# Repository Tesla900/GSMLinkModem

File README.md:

# GSMLinkModem
EFM32TG222F32-QFP48T+BC66-NA/M66 GSM/GPRS/NB-IoT board

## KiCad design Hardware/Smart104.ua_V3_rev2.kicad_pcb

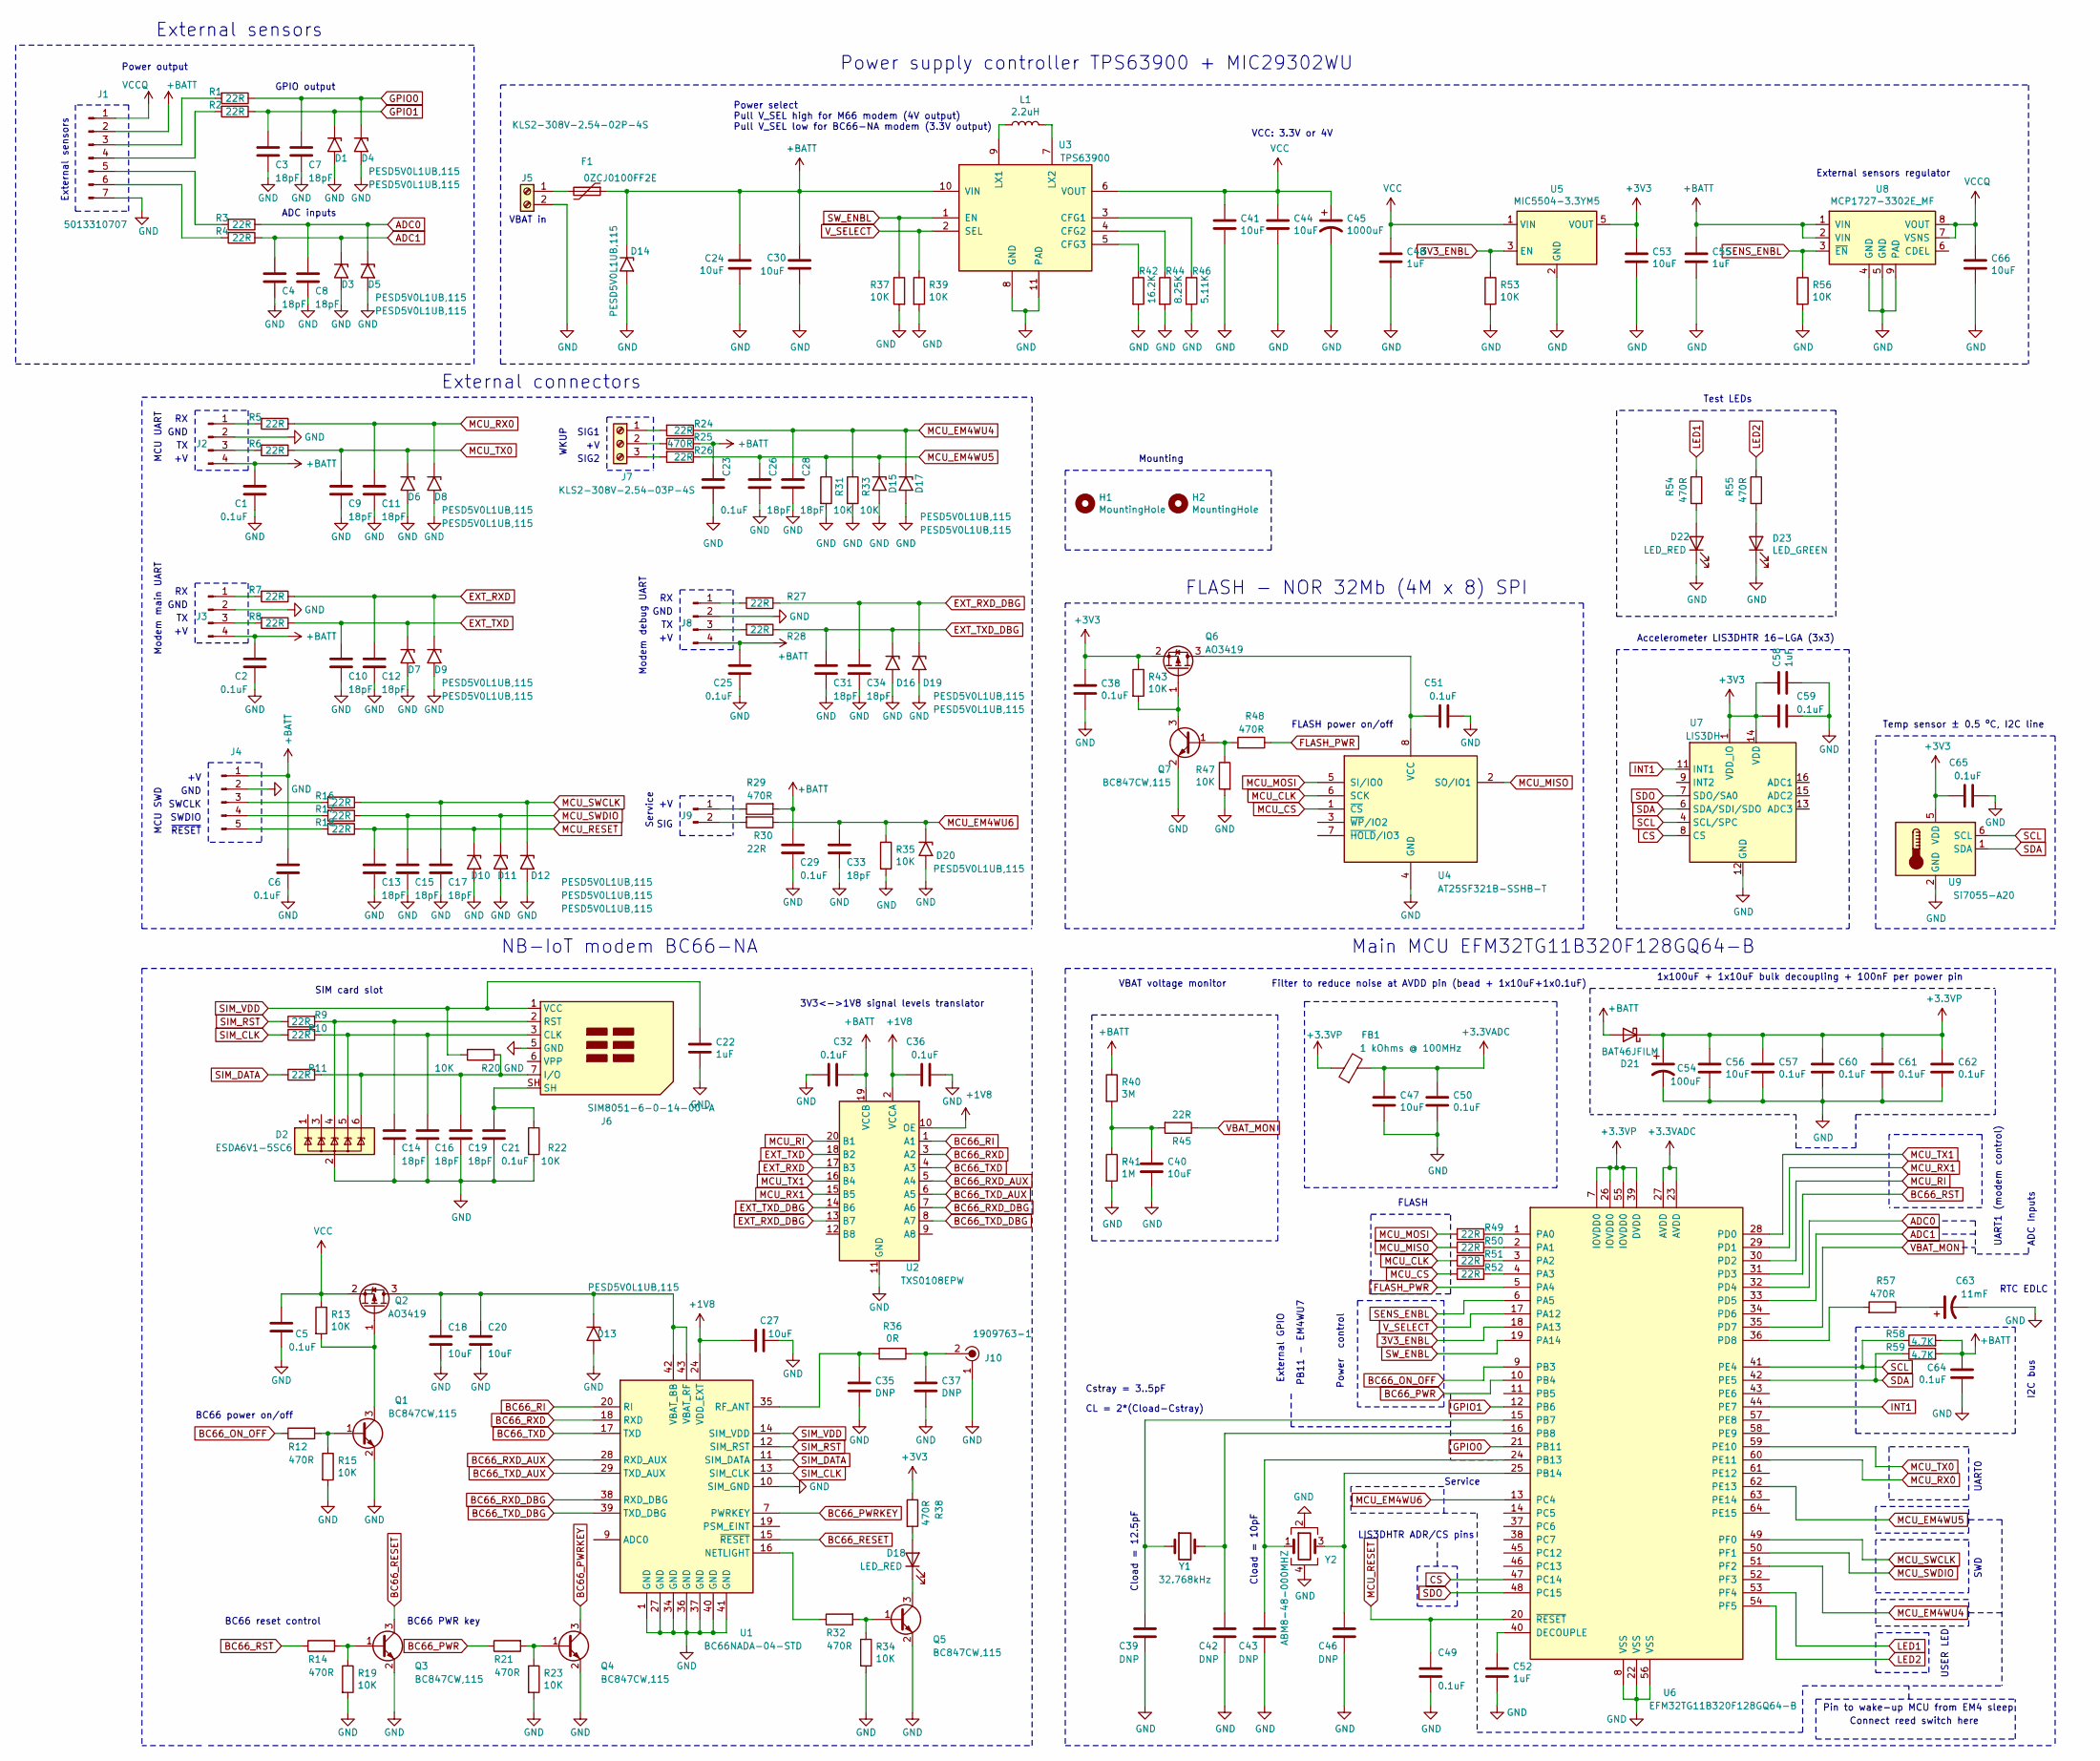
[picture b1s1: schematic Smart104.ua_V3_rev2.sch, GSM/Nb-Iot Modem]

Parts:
C1, C2, C5, C6, C21, C23, C25, C29, C32, C36, C38, C49, C50, C51, C57, C59, C60, C61, C62, C64, C65: 0.1uF; C_0402_1005Metric; Voltage 25V; PartNumber CC0402KRX7R7BB104
C3, C4, C7, C8, C9, C10, C11, C12, C13, C14, C15, C16, C17, C19, C26, C28, C31, C33, C34: 18pF; C_0402_1005Metric; Voltage 50V; PartNumber CC0402JRNPO9BN180
C18, C20, C24, C27, C30, C40, C41, C44, C47, C53, C56, C66: 10uF; C_0805_2012Metric; Voltage 25V; PartNumber CC0805MKX7R7BB106
C22, C48, C52, C55, C58: 1uF; C_0603_1608Metric; Voltage 25V; PartNumber CC0603KRX7R7BB105
C35, C37: DNP; C_0402_1005Metric
C39, C42, C43, C46: DNP; C_0402_1005Metric; Voltage 50V
C45: 1000uF; CP_Radial_D8.0mm_P3.50mm; Voltage 6.3V; PartNumber A750KK108M0JAAE015
C54: 100uF; CP_EIA-3216-18_Kemet-A; Voltage 6.3V; PartNumber TCJA107M006R0150E
C63: 11mF; CAPCP3225X100N; Voltage 3.3V; PartNumber CPH3225A
D1, D3, D4, D5, D6, D7, D8, D9, D10, D11, D12, D13, D14, D15, D16, D17, D19, D20: PESD5V0L1UB,115; D_SOD-523; PartNumber PESD5V0L1UB,115
D2: ESDA6V1-5SC6; SOT-23-6; PartNumber ESDA6V1-5SC6
D18, D22: LED_RED; LED_0603_1608Metric; PartNumber APT1608SURCK
D21: BAT46JFILM; D_SOD-323; PartNumber BAT46JFILM
D23: LED_GREEN; LED_0603_1608Metric; PartNumber APT1608CGCK
F1: 0ZCJ0100FF2E; Fuse_1206_3216Metric; PartNumber 0ZCJ0100FF2E
FB1: 1 kOhms @ 100MHz; L_0402_1005Metric; PartNumber BLM15AG102SN1D
H1, H2: MountingHole; MountingHole_3.2mm_M3; PartNumber Mounting screw M3 DIN965
J1: 5013310707; Molex_Pico-Clasp_501331-0707_1x07-1MP_P1.00mm_Vertical; PartNumber 5013310707
J2, J3, J8: KLS1-207-1-04-S; PinHeader_1x04_P2.54mm_Vertical; PartNumber KLS1-207-1-04-S
J4: KLS1-207-1-05-S; PinHeader_1x05_P2.54mm_Vertical; PartNumber KLS1-207-1-05-S
J5: KLS2-308V-2.54-02P-4S; TerminalBlock_TE_282834-2_1x02_P2.54mm_Horizontal; PartNumber KLS2-308V-2.54-02P-4S
J6: SIM8051-6-0-14-00-A; GCT_SIM8051-6-0-14-00-X-REVD; PartNumber SIM8051-6-0-14-00-A
J7: KLS2-308V-2.54-03P-4S; TerminalBlock_TE_282834-3_1x03_P2.54mm_Horizontal; PartNumber KLS2-308V-2.54-03P-4S
J9: KLS1-207-1-02-S; PinHeader_1x02_P2.54mm_Vertical; PartNumber KLS1-207-1-02-S
J10: 1909763-1; UMCoax_Pin_1909763-1; PartNumber 1909763-1
L1: 2.2uH; L_1008_2520Metric_Pad1.43x2.20mm_HandSolder; PartNumber DFE252010F-2R2M=P2
Q1, Q3, Q4, Q5, Q7: BC847CW,115; SOT-323_SC-70; PartNumber BC847CW,115
Q2, Q6: AO3419; SOT-23; PartNumber AO3419
R1, R2, R3, R4, R5, R6, R7, R8, R9, R10, R11, R16, R17, R18, R24, R26, R27, R28, R30, R45, R49, R50, R51, R52: 22R; R_0402_1005Metric; PartNumber RC0402JR-0722RL
R12, R14, R21, R25, R29, R32, R38, R48, R54, R55, R57: 470R; R_0402_1005Metric; PartNumber RC0402FR-07470RL
R13, R15, R19, R20, R22, R23, R31, R33, R34, R35, R37, R39, R43, R47, R53, R56: 10K; R_0402_1005Metric; PartNumber RC0402FR-0710KL
R36: 0R; R_0402_1005Metric; PartNumber RC0402JR-070RL
R40: 3M; R_0402_1005Metric; PartNumber RC0402FR-073ML
R41: 1M; R_0402_1005Metric; PartNumber RC0402FR-071ML
R42: 16.2K; R_0402_1005Metric; PartNumber RC0402FR-0716K2L
R44: 8.25K; R_0402_1005Metric; PartNumber RC0402FR-078K25L
R46: 5.11K; R_0402_1005Metric; PartNumber RC0402FR-075K11L
R58, R59: 4.7K; R_0402_1005Metric; PartNumber RC0402JR-074K7L
U1: BC66NADA-04-STD; Quectel_BC66; PartNumber BC66NADA-04-STD
U2: TXS0108EPW; TSSOP-20_4.4x6.5mm_P0.65mm; PartNumber TXS0108EPW
U3: TPS63900; DFN-10-1EP_3x3mm_P0.5mm_EP1.65x2.38mm_ThermalVias; PartNumber TPS63900DSKR
U4: AT25SF321B-SSHB-T; SOIC-8_3.9x4.9mm_P1.27mm; PartNumber AT25SF321B-SSHB-T
U5: MIC5504-3.3YM5; SOT-23-5; PartNumber MIC5504-3.3YM5
U6: EFM32TG11B320F128GQ64-B; TQFP-64_10x10mm_P0.5mm; PartNumber EFM32TG11B320F128GQ64-B
U7: LIS3DH; LGA-16_3x3mm_P0.5mm_fixed; PartNumber LIS3DH
U8: MCP1727-3302E_MF; VDFN-8-1EP_2x2mm_P0.5mm_EP0.9x1.7mm; PartNumber MCP1727-3302E_MF
U9: Si7055-A20; DFN-6-1EP_3x3mm_P1mm_EP1.5x2.4mm; PartNumber Si7055-A20
Y1: 32.768kHz; Crystal_SMD_3215-2Pin_3.2x1.5mm; PartNumber CM315D32768DZFT
Y2: ABM8-48-000MHZ; Crystal_SMD_3225-4Pin_3.2x2.5mm; PartNumber ABM8-48.000MHZ-10-1-U-T

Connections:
3V3_ENBL: R53.1, U5.3 (EN), U6.18 (PA13)
+1V8: C27.1, C36.1, U1.24 (VDD_EXT), U2.2 (VCCA), U2.10 (OE)
+3.3VADC: C47.1, C50.1, FB1.2, U6.23 (AVDD), U6.27 (AVDD)
+3.3VP: C54.1, C56.1, C57.1, C60.1, C61.1, C62.1, D21.1 (K), FB1.1, U6.7 (IOVDD0), U6.26 (IOVDD0), U6.39 (DVDD), U6.55 (IOVDD0)
+3V3: C38.1, C53.1, C58.1, C59.2, C65.1, Q6.2 (S), R38.1, R43.1, U5.5 (VOUT), U7.1 (VDD_IO), U7.14 (VDD), U9.5 (VDD)
+BATT: C1.1, C2.1, C6.1, C23.1, C24.1, C25.1, C29.1, C30.1, C32.1, C55.1, C64.1, D14.1 (A1), D21.2 (A), F1.1, J1.2, J2.4, J3.4, J4.1, J8.4, R25.2, R29.2, R40.1, R58.2, R59.2, U2.19 (VCCB), U3.10 (VIN), U8.1 (VIN), U8.2 (VIN)
ADC0: C8.1, D5.1 (A1), R3.1, U6.32 (PD4)
ADC1: C4.1, D3.1 (A1), R4.1, U6.33 (PD5)
BC66_ON_OFF: R12.1, U6.9 (PB3)
BC66_PWR: R21.1, U6.10 (PB4)
BC66_PWRKEY: Q4.3 (C), U1.7 (PWRKEY)
BC66_RESET: Q3.3 (C), U1.15 (~RESET)
BC66_RI: U1.20 (RI), U2.1 (A1)
BC66_RST: R14.1, U6.31 (PD3)
BC66_RXD: U1.18 (RXD), U2.3 (A2)
BC66_RXD_AUX: U1.28 (RXD_AUX), U2.5 (A4)
BC66_RXD_DBG: U1.38 (RXD_DBG), U2.7 (A6)
BC66_TXD: U1.17 (TXD), U2.4 (A3)
BC66_TXD_AUX: U1.29 (TXD_AUX), U2.6 (A5)
BC66_TXD_DBG: U1.39 (TXD_DBG), U2.8 (A7)
CS: U6.47 (PC14), U7.8 (CS)
EXT_RXD: C12.1, D9.1 (A1), R7.1, U2.17 (B3)
EXT_RXD_DBG: C34.1, D19.1 (A1), R27.1, U2.13 (B7)
EXT_TXD: C10.1, D7.1 (A1), R8.1, U2.18 (B2)
EXT_TXD_DBG: C31.1, D16.1 (A1), R28.1, U2.14 (B6)
FLASH_PWR: R48.1, U6.5 (PA4)
GND: C1.2, C2.2, C3.2, C4.2, C5.2, C6.2, C7.2, C8.2, C9.2, C10.2, C11.2, C12.2, C13.2, C14.2, C15.2, C16.2, C17.2, C18.2, C19.2, C20.2, C21.2, C22.2, C23.2, C24.2, C25.2, C26.2, C27.2, C28.2, C29.2, C30.2, C31.2, C32.2, C33.2, C34.2, C35.2, C36.2, C37.2, C38.2, C39.2, C40.2, C41.2, C42.2, C43.2, C44.2, C45.2, C46.2, C47.2, C48.2, C49.2, C50.2, C51.2, C52.2, C53.2, C54.2, C55.2, C56.2, C57.2, C58.2, C59.1, C60.2, C61.2, C62.2, C63.2, C64.2, C65.2, C66.2, D1.2 (A2), D2.2 (GND), D3.2 (A2), D4.2 (A2), D5.2 (A2), D6.2 (A2), D7.2 (A2), D8.2 (A2), D9.2 (A2), D10.2 (A2), D11.2 (A2), D12.2 (A2), D13.2 (A2), D14.2 (A2), D15.2 (A2), D16.2 (A2), D17.2 (A2), D19.2 (A2), D20.2 (A2), D22.1 (K), D23.1 (K), J1.7, J2.2, J3.2, J4.2, J5.2, J6.5 (GND), J8.2, J10.1, Q1.2 (E), Q3.2 (E), Q4.2 (E), Q5.2 (E), Q7.2 (E), R15.2, R19.2, R22.2, R23.2, R31.2, R33.2, R34.2, R35.2, R37.2, R39.2, R41.2, R42.2, R44.2, R46.2, R47.2, R53.2, R56.2, U1.1 (GND), U1.10 (SIM_GND), U1.27 (GND), U1.34 (GND), U1.36 (GND), U1.37 (GND), U1.40 (GND), U1.41 (GND), U2.11 (GND), U3.8 (GND), U3.11 (PAD), U4.4 (GND), U5.2 (GND), U6.8 (VSS), U6.22 (VSS), U6.56 (VSS), U7.5 (GND), U7.10 (GND), U7.12 (GND), U8.4 (GND), U8.5 (GND), U8.9 (PAD), U9.2 (GND), Y2.2, Y2.4
GPIO0: C7.1, D4.1 (A1), R1.1, U6.21 (PB11)
GPIO1: C3.1, D1.1 (A1), R2.1, U6.12 (PB6)
INT1: U6.44 (PE7), U7.11 (INT1)
LED1: R54.1, U6.53 (PF4)
LED2: R55.1, U6.54 (PF5)
MCU_CLK: R51.2, U4.6 (SCK)
MCU_CS: R52.2, U4.1 (~CS~)
MCU_EM4WU4: C28.1, D17.1 (A1), R24.1, R33.1, U6.51 (PF2)
MCU_EM4WU5: C26.1, D15.1 (A1), R26.1, R31.1, U6.62 (PE13)
MCU_EM4WU6: C33.1, D20.1 (A1), R30.1, R35.1, U6.13 (PC4)
MCU_MISO: R50.2, U4.2 (SO/IO1)
MCU_MOSI: R49.2, U4.5 (SI/IO0)
MCU_RESET: C13.1, C49.1, D10.1 (A1), R18.1, U6.20 (~RESET~)
MCU_RI: U2.20 (B1), U6.30 (PD2)
MCU_RX0: C11.1, D8.1 (A1), R5.1, U6.60 (PE11)
MCU_RX1: U2.15 (B5), U6.29 (PD1)
MCU_SWCLK: C17.1, D12.1 (A1), R16.1, U6.49 (PF0)
MCU_SWDIO: C15.1, D11.1 (A1), R17.1, U6.50 (PF1)
MCU_TX0: C9.1, D6.1 (A1), R6.1, U6.59 (PE10)
MCU_TX1: U2.16 (B4), U6.28 (PD0)
unnamed: C14.1, D2.4 (IO3), J6.2 (RST), R9.2
unnamed: C16.1, D2.5 (IO4), J6.3 (CLK), R10.2
unnamed: C18.1, C20.1, D13.1 (A1), Q2.3 (D), U1.42 (VBAT_BB), U1.43 (VBAT_RF)
unnamed: C19.1, D2.6 (IO5), J6.7 (I/O), R11.2, R20.1
unnamed: C21.1, J6.SH, R22.1
unnamed: C35.1, R36.2, U1.35 (RF_ANT)
unnamed: C37.1, J10.2, R36.1
unnamed: C39.1, U6.15 (PB7), Y1.1
unnamed: C40.1, R40.2, R41.1, R45.2
unnamed: C42.1, U6.16 (PB8), Y1.2
unnamed: C43.1, U6.24 (PB13), Y2.1
unnamed: C46.1, U6.25 (PB14), Y2.3
unnamed: C51.1, Q6.3 (D), U4.8 (VCC)
unnamed: C52.1, U6.40 (DECOUPLE)
unnamed: C63.1, R57.1
unnamed: D18.1 (K), Q5.3 (C)
unnamed: D18.2 (A), R38.2
unnamed: D22.2 (A), R54.2
unnamed: D23.2 (A), R55.2
unnamed: F1.2, J5.1
unnamed: J1.3, R1.2
unnamed: J1.4, R2.2
unnamed: J1.5, R3.2
unnamed: J1.6, R4.2
unnamed: J2.1, R5.2
unnamed: J2.3, R6.2
unnamed: J3.1, R7.2
unnamed: J3.3, R8.2
unnamed: J4.3, R16.2
unnamed: J4.4, R17.2
unnamed: J4.5, R18.2
unnamed: J7.1, R24.2
unnamed: J7.2, R25.1
unnamed: J7.3, R26.2
unnamed: J8.1, R27.2
unnamed: J8.3, R28.2
unnamed: J9.1, R29.1
unnamed: J9.2, R30.2
unnamed: L1.1, U3.9 (LX1)
unnamed: L1.2, U3.7 (LX2)
unnamed: Q1.1 (B), R12.2, R15.1
unnamed: Q1.3 (C), Q2.1 (G), R13.2
unnamed: Q3.1 (B), R14.2, R19.1
unnamed: Q4.1 (B), R21.2, R23.1
unnamed: Q5.1 (B), R32.2, R34.1
unnamed: Q6.1 (G), Q7.3 (C), R43.2
unnamed: Q7.1 (B), R47.1, R48.2
unnamed: R32.1, U1.16 (NETLIGHT)
unnamed: R42.1, U3.5 (CFG3)
unnamed: R44.1, U3.4 (CFG2)
unnamed: R46.1, U3.3 (CFG1)
unnamed: R49.1, U6.1 (PA0)
unnamed: R50.1, U6.2 (PA1)
unnamed: R51.1, U6.3 (PA2)
unnamed: R52.1, U6.4 (PA3)
unnamed: R57.2, U6.36 (PD8)
SCL: R58.1, U6.41 (PE4), U7.4 (SCL/SPC), U9.6 (SCL)
SDA: R59.1, U6.42 (PE5), U7.6 (SDA/SDI/SDO), U9.1 (SDA)
SDO: U6.48 (PC15), U7.7 (SDO/SA0)
SENS_ENBL: R56.1, U6.6 (PA5), U8.3 (~EN~)
SIM_CLK: R10.1, U1.13 (SIM_CLK)
SIM_DATA: R11.1, U1.11 (SIM_DATA)
SIM_RST: R9.1, U1.12 (SIM_RST)
SIM_VDD: C22.1, J6.1 (VCC), R20.2, U1.14 (SIM_VDD)
SW_ENBL: R37.1, U3.1 (EN), U6.19 (PA14)
VBAT_MON: R45.1, U6.35 (PD7)
VCC: C5.1, C41.1, C44.1, C45.1, C48.1, Q2.2 (S), R13.1, U3.6 (VOUT), U5.1 (VIN)
VCCQ: C66.1, J1.1, U8.7 (VSNS), U8.8 (VOUT)
V_SELECT: R39.1, U3.2 (SEL), U6.17 (PA12)

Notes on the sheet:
1x100uF + 1x10uF bulk decoupling + 100nF per power pin
CL = 2*(Cload-Cstray)
Cload = 12.5pF
Cstray = 3..5pF
Cload = 10pF
Temp sensor ± 0.5 ºC, I2C line
Main MCU EFM32TG11B320F128GQ64-B
Accelerometer LIS3DHTR 16-LGA (3x3)
FLASH - NOR 32Mb (4M x 8) SPI
Power select Pull V_SEL high for M66 modem (4V output) Pull V_SEL low for BC66-NA modem (3.3V output)
FLASH
FLASH power on/off
BC66 power on/off
BC66 reset control
BC66 PWR key
NB-IoT modem BC66-NA
I2C bus
UART0
SWD
UART1 (modem control)
Power supply controller TPS63900 + MIC29302WU
3V3<->1V8 signal levels translator
VBAT voltage monitor
MCU UART
SIG
GND
Modem main UART
Modem debug UART
MCU SWD
SWCLK
SWDIO
~RESET~
Power control
VBAT in
External connectors
VCC: 3.3V or 4V
SIM card slot
Connect reed switch here
Pin to wake-up MCU from EM4 sleep
Service

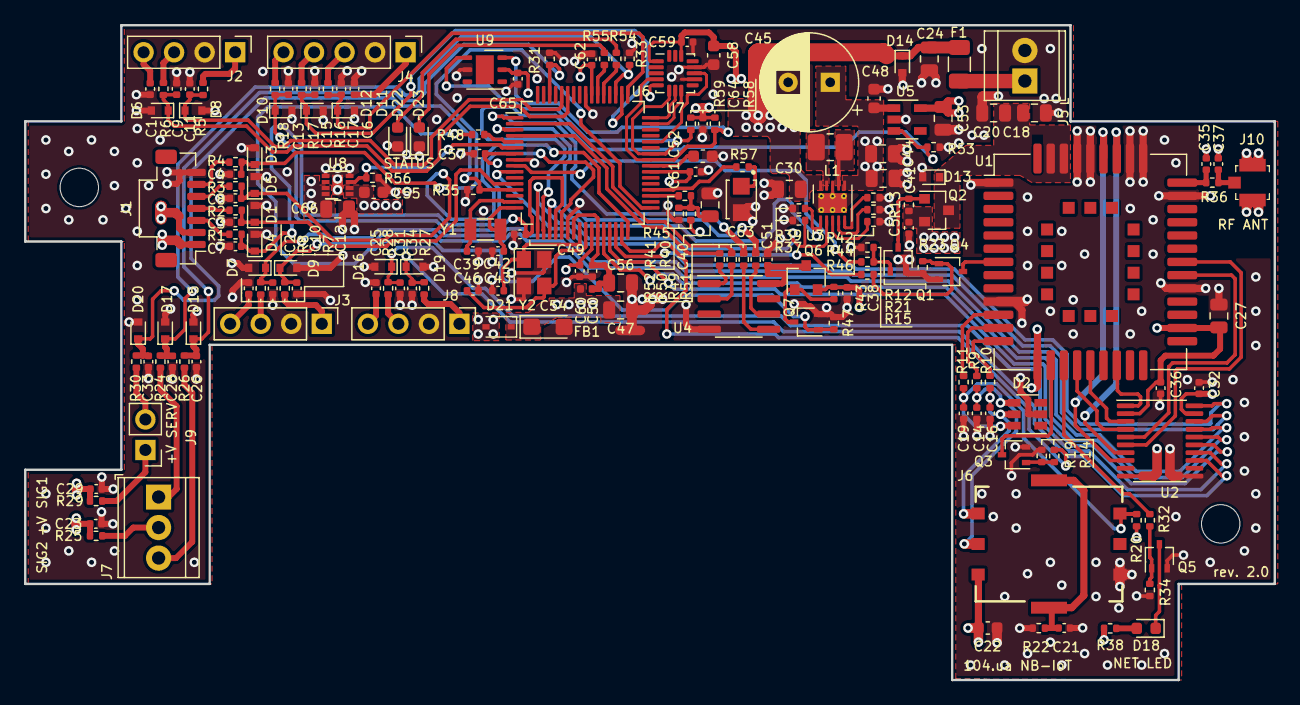
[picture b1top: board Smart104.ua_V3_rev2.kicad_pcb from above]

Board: 4 copper layers, 104.0 x 54.5 mm, 181 parts (0 on the bottom side), 116 nets.

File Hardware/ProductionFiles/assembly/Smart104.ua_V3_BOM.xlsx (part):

Reference | Value/PartNumber | PartNumber | Qty | Description | Link | DoNotPlace Status
C3, C4, C7-C17, C19, C26, C28, C31, C33, C34 | 18pF | CC0402JRNPO9BN180 | 19 | 18pF ±5% 50V Ceramic Capacitor C0G, NP0 0402 (1005 Metric) | https://www.digikey.com/en/products/detail/yageo/CC0402JRNPO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
C35, C37, C39, C42, C43, C46 | DNP | ~ | 6 | ~ | ~ | DNP
C45 | 1000uF | A750KK108M0JAAE015 | 1 | 1000µF 6.3V Aluminum - Polymer Capacitors Radial, Can 15mOhm 2000 Hrs @ 105°C | https://www.digikey.com/en/products/detail/kemet/a750kk108m0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
C22, C48, C52, C55, C58 | 1uF | CC0603KRX7R7BB105 | 5 | 1µF ±10% 16V Ceramic Capacitor X7R 0603 (1608 Metric) | https://www.digikey.com/en/products/detail/yageo/CC0603KRX7R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
C54 | 100uF | TCJA107M006R0150E | 1 | 100µF Molded Tantalum Polymer Capacitor 6.3V 1206 (3216 Metric) 150mOhm @ 100kHz | https://www.digikey.com/en/products/detail/avx-corporation/T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
C18, C20, C24, C27, C30, C40, C41, C44, C47, C53, C56, C66 | 10uF | CC0805MKX7R7BB106 | 12 | 10µF ±20% 16V Ceramic Capacitor X7R 0805 (2012 Metric) | digikey.com/en/products/detail/yageo/CC0805MKX7R7BB106/7164392
C1, C2, C5, C6, C21, C23, C25, C29, C32, C36, C38, C49-C51, C57, C59-C62, C64, 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 | 0.1uF | CC0402KRX7R7BB104 | 21 | 0.1µF ±10% 16V Ceramic Capacitor X7R 0402 (1005 Metric) | https://www.digikey.com/en/products/detail/yageo/CC0402KRX7R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
C63 | 11mF | CPH3225A | 1 | 11mF (EDLC) Supercapacitor 3.3V 1210 (3225 Metric) | https://www.digikey.com/en/products/detail/seiko-instruments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
D2 | ESDA6V1-5SC6 | ESDA6V1-5SC6 | 1 | Clamp 6.1V 100W TVS Diode Array Surface Mount SOT-23-6 | https://www.digikey.com/en/products/detail/stmicroelectronic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
D1, D3-D17, D19, D20 | PESD5V0L1UB,115 | PESD5V0L1UB,115 | 18 | 12V Clamp 3.5A (8/20µs) Ipp Tvs Diode Surface Mount SOD-523 | https://www.digikey.com/en/products/detail/nexperia-usa-inc/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
D21 | BAT46JFILM | BAT46JFILM | 1 | Diode Schottky 100V 150mA (DC), 0.46Vdrop Surface Mount SOD-323 | https://www.digikey.com/en/products/detail/stmicroelectronic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
D18, D22 | LED_RED | APT1608SURCK | 2 | Red 630nm LED Indication - Discrete 1.95V 0603 (1608 Metric) | https://www.digikey.com/en/products/detail/kingbright/APT160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
D23 | LED_GREEN | APT1608CGCK | 1 | Green 570nm LED Indication - Discrete 2.1V 0603 (1608 Metric) | https://www.digikey.com/en/products/detail/kingbright/APT160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
F1 | 0ZCJ0100FF2E | 0ZCJ0100FF2E | 1 | Polymeric PTC Resettable Fuse 6V 1A Ih Surface Mount 1206 (3216 Metric), Concave | https://www.digikey.com/en/products/detail/bel-fuse-inc/0ZCJ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
FB1 | 1 kOhms @ 100MHz | BLM15AG102SN1D | 1 | 1 kOhms @ 100MHz 1 Ferrite Bead 0402 (1005 Metric) 300mA 650mOhm | https://www.digikey.com/en/products/detail/murata-electronic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
H1, H2 | MountingHole | Mounting screw M3 DIN965 | 2 | Mounting screw M3 DIN965 | ~ | DNP
J1 | 5013310707 | 5013310707 | 1 | Connector Header Surface Mount 7 position 0.039" (1.00mm) | https://www.digikey.com/en/products/detail/molex/5013310707/1531476
J2, J3, J8 | KLS1-207-1-04-S | KLS1-207-1-04-S | 3 | Connector Header Through Hole 4 position 0.100" (2.54mm) | http://www.klsele.com/products/connectors/Pin-Headers-Mini-J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
J4 | KLS1-207-1-05-S | KLS1-207-1-05-S | 1 | Connector Header Through Hole 5 position 0.100" (2.54mm) | http://www.klsele.com/products/connectors/Pin-Headers-Mini-J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
J5 | KLS2-308V-2.54-02P-4S | KLS2-308V-2.54-02P-4S | 1 | 2 Position Wire to Board Terminal Block Horizontal with Board 0.100" (2.54mm) T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 | http://www.klsele.com/products/Terminal-blocks/560/278.html
J6 | SIM8051-6-0-14-00-A | SIM8051-6-0-14-00-A | 1 | 6 Position Card Connector NANO SIM Surface Mount, Right Angle Gold | https://www.digikey.com/en/products/detail/gct/SIM8051-6-0-1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
J7 | KLS2-308V-2.54-03P-4S | KLS2-308V-2.54-03P-4S | 1 | 3 Position Wire to Board Terminal Block Horizontal with Board 0.100" (2.54mm) T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 | http://www.klsele.com/products/Terminal-blocks/560/278.html
J9 | KLS1-207-1-02-S | KLS1-207-1-02-S | 1 | Connector Header Through Hole 2 position 0.100" (2.54mm) | http://www.klsele.com/products/connectors/Pin-Headers-Mini-J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
J10 | 1909763-1 | 1909763-1 | 1 | U.FL (UMCC) Connector Jack, Male Pin 50Ohm Surface Mount Solder | https://www.digikey.com/en/products/detail/te-connectivity-a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
L1 | 2.2uH | DFE252010F-2R2M=P2 | 1 | 2.2µH Shielded Inductor 2.3A 97mOhm Max 1008 (2520 Metric) | https://www.digikey.com/en/products/detail/murata-electronic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
Q2, Q6 | AO3419 | AO3419 | 2 | P-Channel 20V 3.5A (Ta) 1.4W (Ta) Surface Mount SOT-23-3L | https://www.digikey.com/en/products/detail/alpha-omega-semic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
Q1, Q3-Q5, Q7 | BC847CW,115 | BC847CW,115 | 5 | Bipolar (BJT) Transistor NPN 45V 100mA 100MHz 200mW Surface Mount SOT-323 | https://www.digikey.com/en/products/detail/nexperia-usa-inc/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
R36 | 0R | RC0402JR-070RL | 1 | 0 Ohms 0.063W, 1/16W Chip Resistor 0402 (1005 Metric) Thick Film | https://www.digikey.com/en/products/detail/yageo/RC0402JR-07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
R40 | 3M | RC0402FR-073ML | 1 | 3 MOhms ±1% 0.125W, 1/8W Chip Resistor 0402 (1005 Metric) Thick Film | https://www.digikey.com/en/products/detail/yageo/RC0402FR-07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
R41 | 1M | RC0402FR-071ML | 1 | 1 MOhms ±1% 0.125W, 1/8W Chip Resistor 0402 (1005 Metric) Thick Film | https://www.digikey.com/en/products/detail/yageo/RC0402FR-07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
R42 | 16.2K | RC0402FR-0716K2L | 1 | 16.2 kOhms ±1% 0.063W, 1/16W Chip Resistor 0402 (1005 Metric) Thick Film | https://www.digikey.com/en/products/detail/yageo/RC0402FR-07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
R44 | 8.25K | RC0402FR-078K25L | 1 | 8.25 kOhms ±1% 0.125W, 1/8W Chip Resistor 0402 (1005 Metric) Thick Film | https://www.digikey.com/en/products/detail/yageo/RC0402FR-07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
R46 | 5.11K | RC0402FR-075K11L | 1 | 5.11 kOhms ±1% 0.125W, 1/8W Chip Resistor 0402 (1005 Metric) Thick Film | https://www.digikey.com/en/products/detail/yageo/RC0402FR-07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
R13, R15, R19, R20, R22, R23, R31, R33-R35, R37, R39, R43, R47, R53, R56 | 10K | RC0402FR-0710KL | 16 | 10 kOhms ±1% 0.063W, 1/16W Chip Resistor 0402 (1005 Metric) Thick Film | https://www.digikey.com/en/products/detail/yageo/RC0402FR-07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
R12, R14, R21, R25, R29, R32, R38, R48, R54, R55, R57 | 470R | RC0402FR-07470RL | 11 | 470 Ohms ±5% 0.125W, 1/8W Chip Resistor 0402 (1005 Metric) Thick Film | https://www.digikey.com/en/products/detail/yageo/RC0402FR-07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
R1-R11, R16-R18, R24, R26-R28, R30, R45, R49-R52 | 22R | RC0402JR-0722RL | 24 | 22 Ohms ±5% 0.125W, 1/8W Chip Resistor 0402 (1005 Metric) Thick Film | https://www.digikey.com/en/products/detail/yageo/RC0402JR-07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
R58, R59 | 4.7K | RC0402JR-074K7L | 2 | 4.7 kOhms ±5% 0.125W, 1/8W Chip Resistor 0805 (2012 Metric) Thick Film | https://www.digikey.com/en/products/detail/yageo/RC0402JR-07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
U1 | BC66NADA-04-STD | BC66NADA-04-STD | 1 | Cellular GPRS, GSM, LTE, NB-IOT Transceiver Module Antenna Not Included Surface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 | https://www.digikey.com/en/products/detail/quectel/BC66NADA-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
U2 | TXS0108EPW | TXS0108EPW | 1 | Voltage Level Translator Bidirectional 1 Circuit 8 Channel 60Mbps 20-TSSOP | https://www.digikey.com/en/products/detail/texas-instruments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
U3 | TPS63900 | TPS63900DSKR | 1 | Buck-Boost Switching Regulator IC Positive Programmable 1.8V 1 Output 10-WFDFN 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 | https://www.digikey.com/en/products/detail/texas-instruments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
U4 | AT25SF321B-SSHB-T | AT25SF321B-SSHB-T | 1 | FLASH - NOR Memory IC 32Mb (4M x 8) SPI - Quad I/O 108MHz 8-SOIC | https://www.digikey.com/en/products/detail/adesto-technologi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
U5 | MIC5504-3.3YM5 | MIC5504-3.3YM5 | 1 | Linear Voltage Regulator IC 1 Output 3.3V 300mA SOT-23-5 | https://www.digikey.com/en/products/detail/microchip-technol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
U6 | EFM32TG11B320F128GQ64-B | EFM32TG11B320F128GQ64-B | 1 | ARM Cortex-M0+ Tiny Gecko 1 Microcontroller IC 32-Bit 48MHz 128KB (128K x 8) FL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 | https://www.digikey.com/en/products/detail/silicon-labs/EFM3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
U7 | LIS3DH | LIS3DH | 1 | Accelerometer X, Y, Z Axis ±2g, 4g, 8g, 16g 0.5Hz ~ 625Hz 16-LGA (3x3) | https://www.digikey.com/en/products/detail/stmicroelectronic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 | DNP
U8 | MCP1727-3302E_MF | MCP1727-3302E_MF | 1 | Linear Voltage Regulator IC 1 Output 3.3V 1.5A 8-DFN-EP (3x3) | https://www.digikey.com/en/products/detail/microchip-technol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

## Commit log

2020-11-24 new: Initial commit
2020-11-24 new: Work in progress
2020-12-09 new: Rev. 1.0
2020-12-10 new: Rev. 1.0 gerbers/fixes
2020-12-14 new: Rev. 1.0 gerbers/fixes_2
2020-12-20 fix: Rev. 1.0 connector added, pcb fixes
2020-12-21 fix: Rev. 1.0 production files added
2021-01-17 new: Rev. 1.0 LGA-16 footprint fixed, minor fixes
